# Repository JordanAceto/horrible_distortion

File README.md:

## stm32 based bitcrusher pedal

## Repository organization
- Schematics, BOM, kicad files, and gerbers are in the [hardware](https://github.com/JordanAceto/bit_crusher_pedal/tree/master/hardware) directory.
- Source files and instructions on how to flash the firmware are in the [firmware](https://github.com/JordanAceto/bit_crusher_pedal/tree/master/firmware) directory.
- The [reference_docs](https://github.com/JordanAceto/bit_crusher_pedal/tree/master/reference_docs) directory contains various datasheets for the components used by the system.
- There is a [user manual](https://github.com/JordanAceto/bit_crusher_pedal/tree/master/user_manual.pdf) in the root directory.

---

## License:
-  hardware: CC by 4.0
-  software: MIT license
-  by: Jordan Aceto

---

## Status of the project:

revision | schematic | pcb layout | firmware | built and tested |
---------|-----------|------------|----------|------------------|
1.1      | &#9745;   | &#9745;    | &#9745;  | &#9745;          |

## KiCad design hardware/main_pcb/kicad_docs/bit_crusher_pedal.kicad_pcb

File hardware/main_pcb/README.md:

# main pcb:

<br /><br />

## The main pcb contains all the circuitry for the effect, excluding the 1/4" jacks, 9vdc power entry jack, and true-bypass footswitch. These off-board components are connected to the main pcb with soldered flying wires. 

<br /><br />

---

## Description of the audio circuit:

The audio signal is immediately buffered by a FET source-follower which provides a high impedance input as expected by guitars and other musical instruments.

The signal is then compressed by 1/2 of an NE570 compandor chip configured as a compressor. This compression squishes the audio signal into a reduced range so that both quiet and loud signals take up enough ADC resolution for the algorithm to work with.

The compressed audio signal is then sent to a variable gain amplifier where the user can adjust the magnitude of the signal entering the ADC to taste. This amplifier also acts as a clipping amplifier to protect the ADC from signals outside of its voltage range. A bi-color LED acts as a signal strength and clipping indicator as an aid to the user in setting a healthy signal level.

Now the signal is read in to the microcontroller by an onboard ADC and processed internally.

The processed digitized signal is then converted back to an analog signal by the microcontrollers onboard DAC.

The output of the DAC is fed into an opamp low pass filter to attenuate very high frequencies outside of the audio band.

The filtered processed signal is finally sent to the other half of the NE570 configured as an expandor this time. This restores the dynamic range of the original audio signal.

<br /><br />

---

## Description of the control circuit:

Control voltage signals for bit-depth and sample-rate are generated by opamps. The contribution of onboard rotary potentiometers and optional external control voltage signals are summed and inverted.

The opamp control voltage generators also act as protection for the ADC. Control voltages outside of the safe range for the ADC will be harmlessly clipped by the opamps.

These control voltage signals are then read in to the microcontroller by onboard ADCs and used to process the audio signals.

The external CV input ports can accept either voltage signals in the range of 0 volts to +5 volts, or they can accept an expression pedal connected to a TRS jack.

Because different brands of expression pedals use different potentiometer values, trim-pots are included to calibrate the device for various expression pedals.

<br /><br />

---

## Errata:

A port for an optional on/off LED indicator is included on the main pcb. If desired attach a panel mounted LED to this port through a spare pole of a bypass switch.

An SWD header is used to program and debug the STM32 microcontroller.

This project is intended as a "guitar pedal" type effects box which fits in a Hammond 'BB' style enclosure. The main pcb is affixed to the enclosure with the pcb mounted potentiometers. Flying wires are then routed to the chassis mounted 1/4" jacks, 9vdc power input jack, and true-bypass footswitch.

There are optional mounting holes if a different mechanical setup is desired.

<br /><br />

---

## Top and bottom render of the main pcb:

<br /><br />

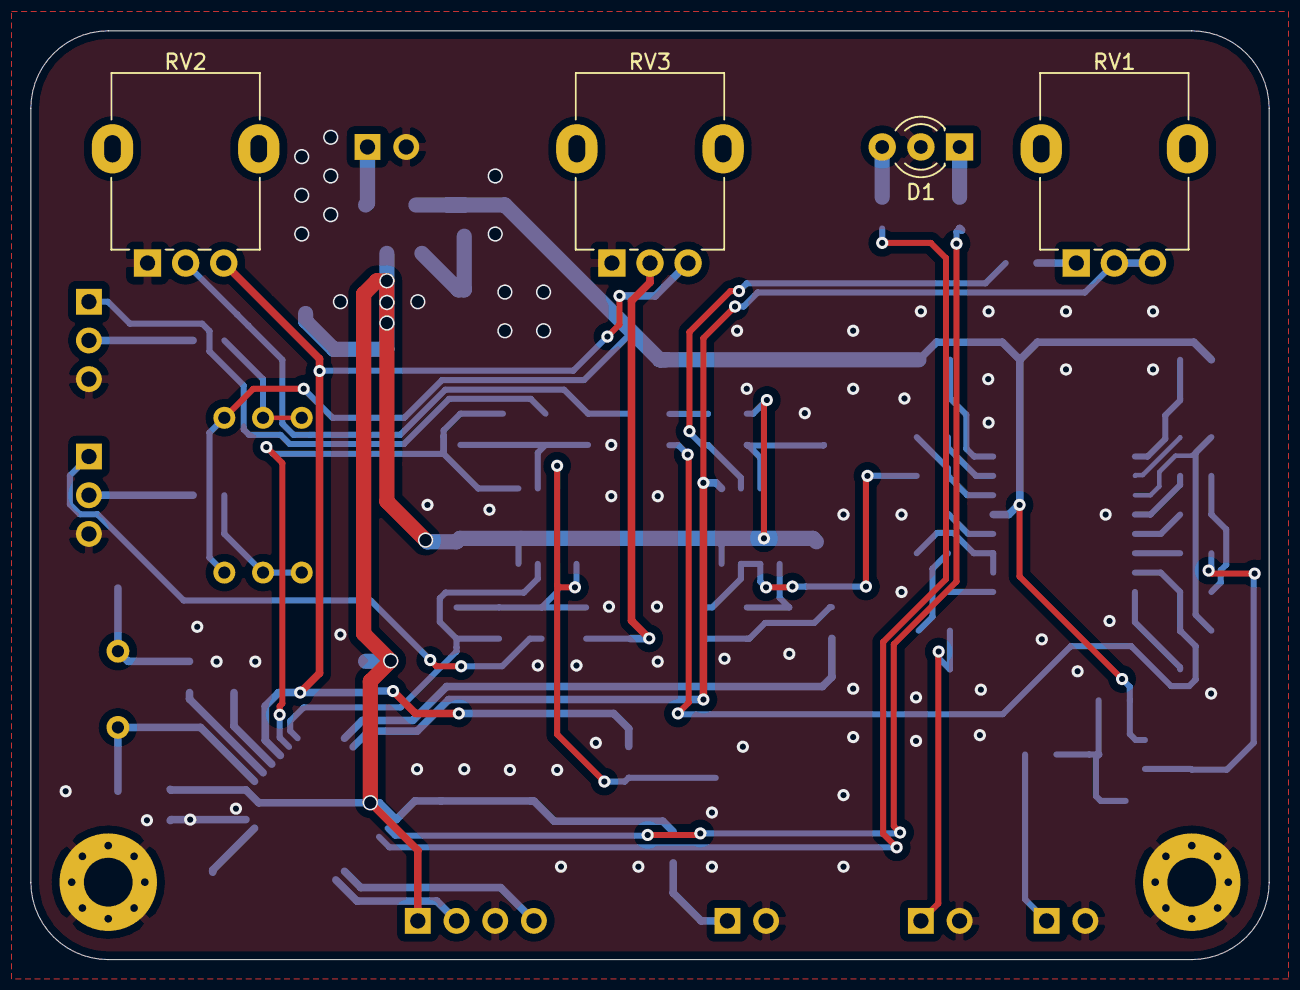
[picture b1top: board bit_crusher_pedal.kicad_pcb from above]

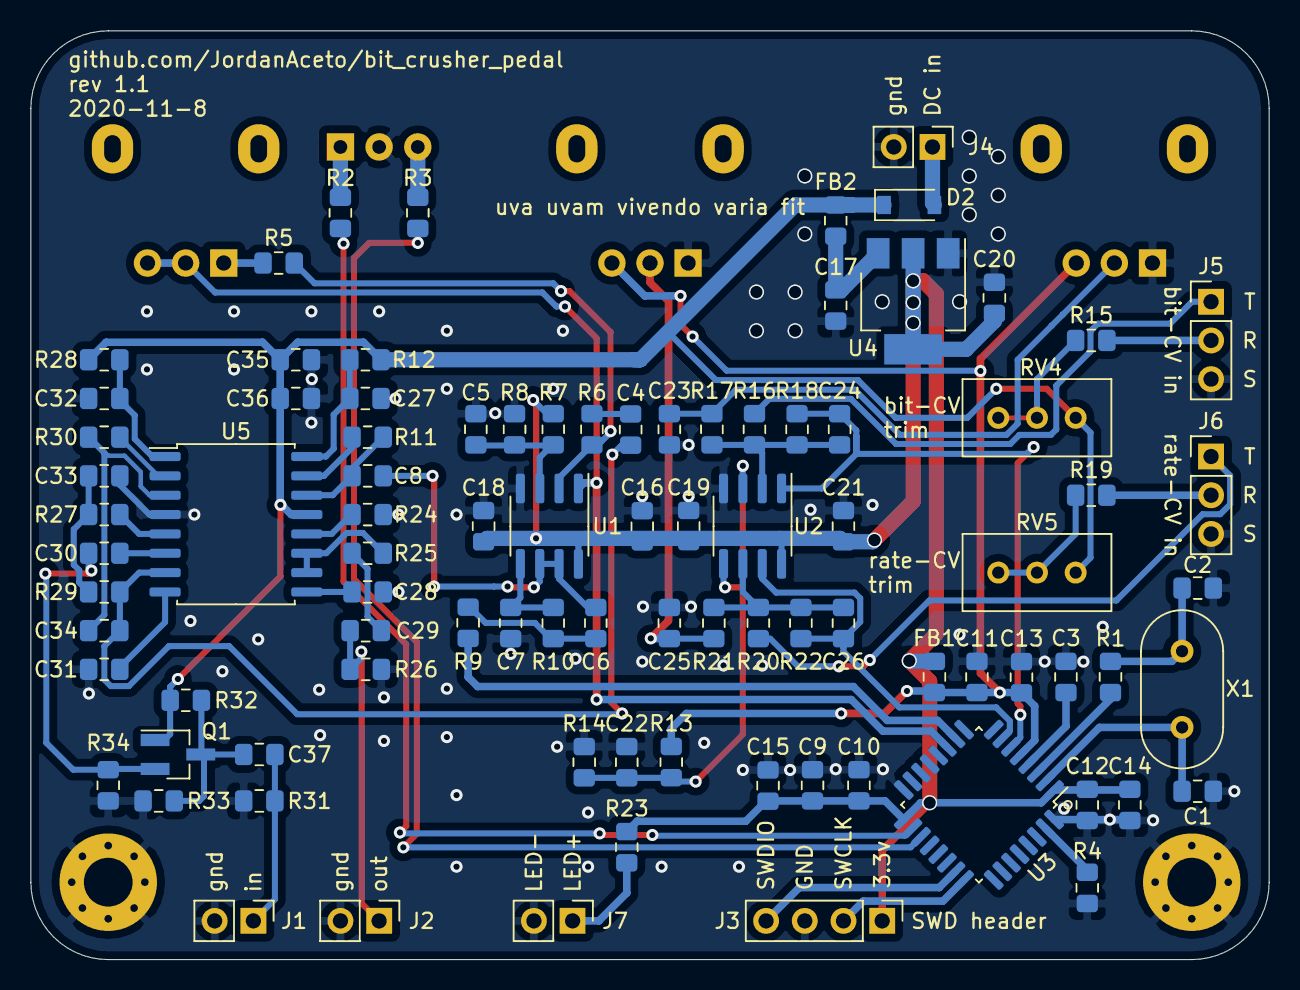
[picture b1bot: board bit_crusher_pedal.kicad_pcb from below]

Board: 2 copper layers, 81.3 x 61.0 mm, 96 parts (90 on the bottom side), 59 nets.

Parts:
C1, C2: 20pF; C_0805_2012Metric_Pad1.15x1.40mm_HandSolder
C3, C5, C10, C12, C14, C15, C16, C18, C19, C21, C22, C23, C25, C36: 100nF; C_0805_2012Metric_Pad1.15x1.40mm_HandSolder
C4, C27, C30, C32: 220nF; C_0805_2012Metric_Pad1.15x1.40mm_HandSolder
C6, C7: 1nF; C_0805_2012Metric_Pad1.15x1.40mm_HandSolder
C8: 470nF; C_0805_2012Metric_Pad1.15x1.40mm_HandSolder
C9: 4.7uF; C_0805_2012Metric_Pad1.15x1.40mm_HandSolder
C11: 1uF; C_0805_2012Metric_Pad1.15x1.40mm_HandSolder
C13, C24, C26, C37: 10nF; C_0805_2012Metric_Pad1.15x1.40mm_HandSolder
C17, C20, C29, C33, C35: 10uF; C_0805_2012Metric_Pad1.15x1.40mm_HandSolder
C28, C31: 220pF; C_0805_2012Metric_Pad1.15x1.40mm_HandSolder
C34: 2.2uF; C_0805_2012Metric_Pad1.15x1.40mm_HandSolder
D1: rg_clipping_LED; LED_D3.0mm-3
D2: B5819W; D_SOD-123
FB1, FB2: 100R @ 100MHz; L_0805_2012Metric_Pad1.15x1.40mm_HandSolder
H1, H2: MountingHole_Pad; MountingHole_3.2mm_M3_Pad_Via
J1: audio_input; PinHeader_1x02_P2.54mm_Vertical
J2: audio_output; PinHeader_1x02_P2.54mm_Vertical
J3: SWD_header; PinHeader_1x04_P2.54mm_Vertical
J4: 9v_DC_in; PinHeader_1x02_P2.54mm_Vertical
J5: extern_resolution_CV; PinHeader_1x03_P2.54mm_Vertical
J6: extern_sample_rate_CV; PinHeader_1x03_P2.54mm_Vertical
J7: to_LED; PinHeader_1x02_P2.54mm_Vertical
Q1: MMBF5457; SOT-23_Handsoldering
R1: 390; R_0805_2012Metric_Pad1.15x1.40mm_HandSolder
R2, R3, R23: 330; R_0805_2012Metric_Pad1.15x1.40mm_HandSolder
R4, R6, R11, R15, R19, R30, R34: 10k; R_0805_2012Metric_Pad1.15x1.40mm_HandSolder
R5: 2k2; R_0805_2012Metric_Pad1.15x1.40mm_HandSolder
R7, R8, R13, R14: 1k8; R_0805_2012Metric_Pad1.15x1.40mm_HandSolder
R9, R10: 8k2; R_0805_2012Metric_Pad1.15x1.40mm_HandSolder
R12, R28, R31, R32, R33: 2M2; R_0805_2012Metric_Pad1.15x1.40mm_HandSolder
R16, R20: 100k; R_0805_2012Metric_Pad1.15x1.40mm_HandSolder
R17, R18, R21, R22: 68k; R_0805_2012Metric_Pad1.15x1.40mm_HandSolder
R24: opt; R_0805_2012Metric_Pad1.15x1.40mm_HandSolder
R25: 560; R_0805_2012Metric_Pad1.15x1.40mm_HandSolder
R26: 1M; R_0805_2012Metric_Pad1.15x1.40mm_HandSolder
R27, R29: 22k; R_0805_2012Metric_Pad1.15x1.40mm_HandSolder
RV1: 100k; Potentiometer_Alpha_RD901F-40-00D_Single_Vertical
RV2, RV3: 10k; Potentiometer_Alpha_RD901F-40-00D_Single_Vertical
RV4, RV5: 100k; Potentiometer_Bourns_3296W_Vertical
U1, U2: MCP6002-xP; SOIC-8_3.9x4.9mm_P1.27mm
U3: STM32F334K6Tx; LQFP-32_7x7mm_P0.8mm
U4: AMS1117-3.3; SOT-223-3_TabPin2
U5: NE570; SOIC-16W_7.5x10.3mm_P1.27mm
X1: 8MHz; Resonator-2Pin_W10.0mm_H5.0mm

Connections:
+3.3VA: C11.1, C13.1, FB1.1, R13.1, RV2.3, RV3.3, U3.5
+3V3: C9.1, C10.1, C12.1, C14.1, C15.1, C16.1, C18.1, C19.1, C20.1, C21.1, FB1.2, J3.1, R7.2, R23.2, U1.8, U2.8, U3.1, U3.17, U4.2
+9V: C35.1, C36.1, D2.1, FB2.2, Q1.1, R12.1, R28.1, R32.2, RV4.3, RV5.3, U5.13
/compressor/compressor_in: C37.2, J1.1, R31.2
/control_voltage_generator/CV_amp_bias: C22.1, R13.2, R14.1, U2.3, U2.5
/expander/expander_in: C6.1, C8.2, U1.6, U1.7
/expander/expander_out: C29.1, J2.1, R26.2
/microcontroller/ADC_in: RV1.2, RV1.3, U1.1, U3.11
/microcontroller/BOOT0: R4.1, U3.31
/microcontroller/DAC_out: R9.2, U3.10
/microcontroller/NRST: C3.1, U3.4
/microcontroller/SWCLK: J3.2, U3.24
/microcontroller/SWDIO: J3.4, U3.23
/microcontroller/resolution_CV_in: C24.1, R18.1, U2.1, U3.6
/microcontroller/sample_rate_CV_in: C26.1, R22.1, U2.7, U3.7
/variable_gain_amp/audio_in: C4.2, C34.2, R29.1, U5.7
GND: C1.2, C2.2, C3.2, C5.1, C7.1, C9.2, C10.2, C11.2, C12.2, C13.2, C14.2, C15.2, C16.2, C17.2, C18.2, C19.2, C20.2, C21.2, C22.2, C23.2, C25.2, C27.1, C28.2, C31.1, C32.1, C33.1, C35.2, C36.2, D1.2, H1.1, H2.1, J1.2, J2.2, J3.3, J4.2, J5.3, J6.3, J7.2, R4.2, R8.1, R14.2, R24.2, R26.1, R31.1, R33.1, R34.1, RV2.1, RV3.1, U1.4, U2.4, U3.16, U3.32, U4.1, U5.4
unnamed: C1.1, U3.2, X1.1
unnamed: C2.1, R1.2, X1.2
unnamed: C4.1, R6.2
unnamed: C5.2, R7.1, R8.2, U1.3
unnamed: C6.2, R9.1, R10.2
unnamed: C7.2, R10.1, U1.5
unnamed: C8.1, R11.2, U5.14
unnamed: C17.1, FB2.1, U4.3
unnamed: C23.1, R17.2, RV2.2
unnamed: C24.2, R16.1, R17.1, R18.2, U2.2
unnamed: C25.1, R21.2, RV3.2
unnamed: C26.2, R20.1, R21.1, R22.2, U2.6
unnamed: C27.2, R12.2, U5.16
unnamed: C28.1, U5.9
unnamed: C29.2, R25.1
unnamed: C30.1, U5.6
unnamed: C30.2, Q1.2, R34.2
unnamed: C31.2, U5.8
unnamed: C32.2, R28.2, U5.1
unnamed: C33.2, R27.1, R29.2
unnamed: C34.1, R30.1, U5.3
unnamed: C37.1, Q1.3, R32.1, R33.2
unnamed: D1.1, R2.1
unnamed: D1.3, R3.1
unnamed: D2.2, J4.1
unnamed: J5.1, R16.2
unnamed: J5.2, R15.2
unnamed: J6.1, R20.2
unnamed: J6.2, R19.2
unnamed: J7.1, R23.1
unnamed: R1.1, U3.3
unnamed: R2.2, U3.18
unnamed: R3.2, U3.19
unnamed: R5.1, RV1.1
unnamed: R5.2, R6.1, U1.2
unnamed: R11.1, U5.15
unnamed: R15.1, RV4.1, RV4.2
unnamed: R19.1, RV5.1, RV5.2
unnamed: R24.1, U5.12
unnamed: R25.2, U5.10, U5.11
unnamed: R27.2, U5.5
unnamed: R30.2, U5.2

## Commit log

2020-07-28 initial commit, main pcb started
2020-07-29 start front panel
2020-07-29 start jack panel
2020-07-29 generate BOM
2020-07-29 generate schematic
2020-07-29 generate gerbers
2020-07-29 generate jack panel gerbers
2020-07-29 generate front panel gerbers
2020-07-30 fix jack panel issue where front mask was missing
2020-08-04 update readme with checklist
2020-08-05 add datasheets and manuals
2020-08-12 add licenses
2020-08-12 update readme with license info
2020-08-12 add some pics
2020-08-12 add pics
2020-08-17 add compander
2020-08-17 add compander and FET datasheets
2020-08-17 reorganize directory structure
2020-08-18 add rev 1 main pcb docs
2020-08-18 fix minor silkscreen issue
2020-08-18 switch trimpot rotation
2020-08-20 change gain pot to 100k
2020-08-22 update gitignore for binaries
2020-08-22 add template for firmware development
2020-08-22 add firmware readme
2020-08-22 add some config code
2020-08-22 move flash latency into RCC init
2020-08-22 add some ADC code and test the ADC
2020-08-22 test the ADC
2020-08-23 add some code to test DAC1
2020-08-23 move peripherals into .h and .c files, test ADC2 and DAC
2020-08-23 fix bug insystic delay
2020-08-23 use TIM6 to trigger ADC2
2020-08-23 remove unnecesary TIM6 NVIC config
2020-08-23 add bit-crusher files, work in progress
2020-08-24 get DMA working, tidy up
2020-08-24 remove unused systic includes
2020-08-24 clean up formatting
2020-08-24 apply bit-crushing algorithm in ISRs
2020-08-24 tidy up interrupts
2020-08-24 experiment with crusher algo scaling
2020-08-24 change optimization to -Os
2020-08-24 add LED signal strength indicator
2020-08-24 tidy up LED signal indicator
2020-08-24 slight tweak to the crusher algo
2020-08-27 clean up some tabs vs spaces issues
2020-08-27 re-order some ADC2 init code for better clarity
2020-08-27 remove old DMA comment
2020-11-08 rev 1.1, fix silkscreen, flip trimpots, adjust hpf
2020-11-08 flip trimpots again, hopefully right this time
2020-11-09 rearrange schematic pages
2020-11-09 fix page order in schematic pdf
2020-11-11 update main pcb readme
2020-11-14 add info to readme files
2020-11-14 add note about the algorithm to readme
2020-11-14 fix typos in readme
2020-11-14 add glamour shot
2020-11-14 update readme with glamour shot, remove old info
2020-11-14 add user manual pdf
2020-11-14 rejigger some system clock init comments
2020-11-14 update readme with directory info
2020-11-16 add offboard wiring diagram
2020-12-20 small comment typo
2020-12-20 tick boxes after successful build
2021-06-10 add DC jack and enclosure datasheets
2021-06-11 add drill guides
2021-06-11 fix incorrect file names
2021-06-11 add drill guide readme
2021-06-22 big firmware reorganization
2021-06-22 reorder schematic pages

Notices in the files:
hardware/main_pcb/kicad_docs/bit_crusher_pedal.kicad_pcb:
License: CC by 4.0
